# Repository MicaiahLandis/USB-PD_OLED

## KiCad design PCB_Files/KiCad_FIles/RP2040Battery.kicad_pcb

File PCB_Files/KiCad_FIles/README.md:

This Folder Had All KiCad Project files

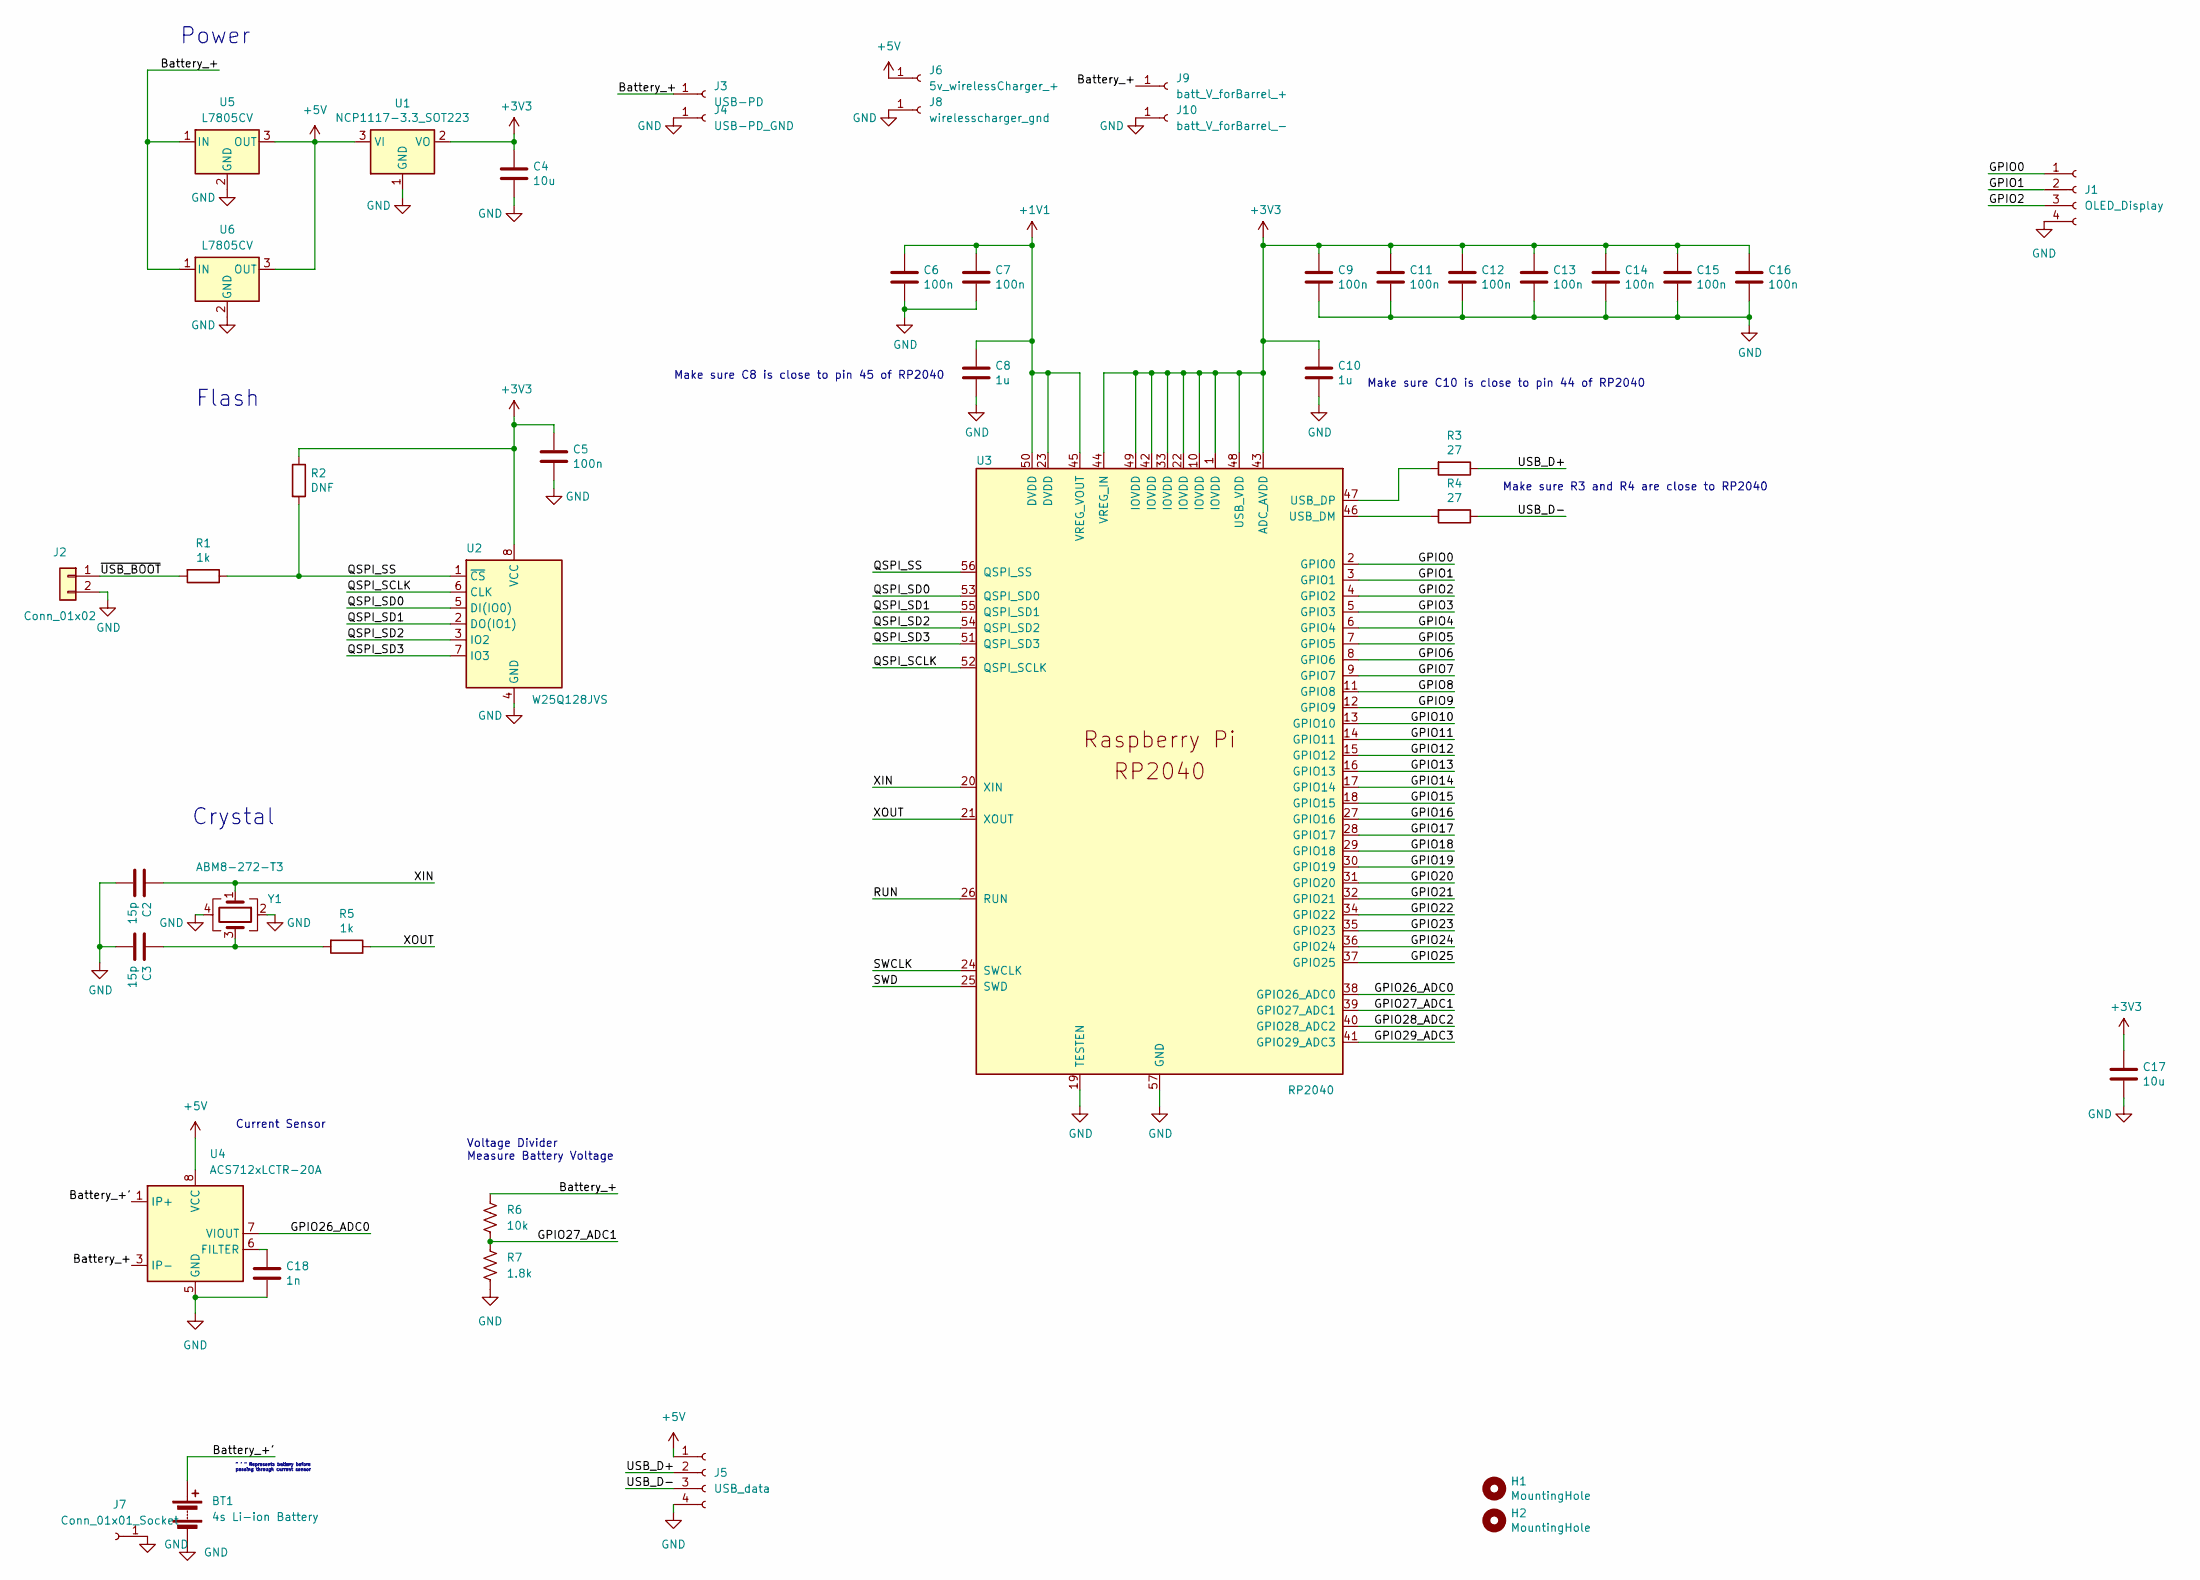
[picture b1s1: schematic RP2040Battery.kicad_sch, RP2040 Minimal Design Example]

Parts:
BT1: 4s Li-ion Battery; TestPoint_Pad_4.0x4.0mm
C2, C3: 15p; C_0402_1005Metric
C4, C17: 10u; C_0805_2012Metric
C5, C6, C7, C9, C11, C12, C13, C14, C15, C16: 100n; C_0402_1005Metric
C8, C10: 1u; C_0402_1005Metric
C18: 1n; C_0402_1005Metric
H1, H2: MountingHole; MountingHole_2.7mm_M2.5
J1: OLED_Display; PinHeader_1x04_P2.54mm_Vertical
J2: Conn_01x02; PinHeader_1x02_P2.54mm_Vertical
J3: USB-PD; SolderWire-2.5sqmm_1x01_D2.4mm_OD3.6mm
J4: USB-PD_GND; SolderWire-2.5sqmm_1x01_D2.4mm_OD3.6mm
J5: USB_data; PinHeader_1x04_P2.54mm_Vertical
J6: 5v_wirelessCharger_+; TestPoint_Pad_2.0x2.0mm
J7: Conn_01x01_Socket; TestPoint_Pad_4.0x4.0mm
J8: wirelesscharger_gnd; TestPoint_Pad_2.0x2.0mm
J9: batt_V_forBarrel_+; TestPoint_Pad_2.0x2.0mm
J10: batt_V_forBarrel_-; TestPoint_Pad_2.0x2.0mm
R1, R5: 1k; R_0402_1005Metric
R2: DNF; R_0402_1005Metric
R3, R4: 27; R_0402_1005Metric
R6: 10k; R_0402_1005Metric
R7: 1.8k; R_0402_1005Metric
U1: NCP1117-3.3_SOT223; SOT-223-3_TabPin2
U2: W25Q128JVS; SOIC-8_5.23x5.23mm_P1.27mm
U3: RP2040; RP2040-QFN-56
U4: ACS712xLCTR-20A; SOIC-8_3.9x4.9mm_P1.27mm
U5, U6: L7805CV; SIPAK-1EP_Horizontal_TabDown
Y1: ABM8-272-T3; Crystal_SMD_3225-4Pin_3.2x2.5mm

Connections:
+1V1: C6.1, C7.1, C8.1, U3.23 (DVDD), U3.45 (VREG_VOUT), U3.50 (DVDD)
+3V3: C4.1, C5.1, C9.1, C10.1, C11.1, C12.1, C13.1, C14.1, C15.1, C16.1, C17.1, R2.1, U1.2 (VO), U2.8 (VCC), U3.1 (IOVDD), U3.10 (IOVDD), U3.22 (IOVDD), U3.33 (IOVDD), U3.42 (IOVDD), U3.43 (ADC_AVDD), U3.44 (VREG_IN), U3.48 (USB_VDD), U3.49 (IOVDD)
+5V: J5.1, J6.1, U1.3 (VI), U4.8 (VCC), U5.3 (OUT), U6.3 (OUT)
/Battery_+: J3.1, J9.1, R6.1, U4.3 (IP-), U4.4 (IP-), U5.1 (IN), U6.1 (IN); also elsewhere on the board
/Battery_+': BT1.1 (+), U4.1 (IP+), U4.2 (IP+)
/GPIO0: J1.1, U3.2 (GPIO0)
/GPIO1: J1.2, U3.3 (GPIO1)
/GPIO2: J1.3, U3.4 (GPIO2)
/GPIO3: U3.5 (GPIO3)
/GPIO4: U3.6 (GPIO4)
/GPIO5: U3.7 (GPIO5)
/GPIO6: U3.8 (GPIO6)
/GPIO7: U3.9 (GPIO7)
/GPIO8: U3.11 (GPIO8)
/GPIO9: U3.12 (GPIO9)
/GPIO10: U3.13 (GPIO10)
/GPIO11: U3.14 (GPIO11)
/GPIO12: U3.15 (GPIO12)
/GPIO13: U3.16 (GPIO13)
/GPIO14: U3.17 (GPIO14)
/GPIO15: U3.18 (GPIO15)
/GPIO16: U3.27 (GPIO16)
/GPIO17: U3.28 (GPIO17)
/GPIO18: U3.29 (GPIO18)
/GPIO19: U3.30 (GPIO19)
/GPIO20: U3.31 (GPIO20)
/GPIO21: U3.32 (GPIO21)
/GPIO22: U3.34 (GPIO22)
/GPIO23: U3.35 (GPIO23)
/GPIO24: U3.36 (GPIO24)
/GPIO25: U3.37 (GPIO25)
/GPIO26_ADC0: U3.38 (GPIO26_ADC0), U4.7 (VIOUT)
/GPIO27_ADC1: R6.2, R7.1, U3.39 (GPIO27_ADC1)
/GPIO28_ADC2: U3.40 (GPIO28_ADC2)
/GPIO29_ADC3: U3.41 (GPIO29_ADC3)
/QSPI_SCLK: U2.6 (CLK), U3.52 (QSPI_SCLK)
/QSPI_SD0: U2.5 (DI(IO0)), U3.53 (QSPI_SD0)
/QSPI_SD1: U2.2 (DO(IO1)), U3.55 (QSPI_SD1)
/QSPI_SD2: U2.3 (IO2), U3.54 (QSPI_SD2)
/QSPI_SD3: U2.7 (IO3), U3.51 (QSPI_SD3)
/QSPI_SS: R1.1, R2.2, U2.1 (~CS), U3.56 (QSPI_SS)
/RUN: U3.26 (RUN)
/SWCLK: U3.24 (SWCLK)
/SWD: U3.25 (SWD)
/USB_D+: J5.2, R3.1
/USB_D-: J5.3, R4.1
/XIN: C2.1, U3.20 (XIN), Y1.1
/XOUT: R5.1, U3.21 (XOUT)
/~USB_BOOT: J2.1, R1.2
GND: BT1.2 (-), C2.2, C3.2, C4.2, C5.2, C6.2, C7.2, C8.2, C9.2, C10.2, C11.2, C12.2, C13.2, C14.2, C15.2, C16.2, C17.2, C18.2, J1.4, J2.2, J4.1, J5.4, J7.1, J8.1, J10.1, R7.2, U1.1 (GND), U2.4 (GND), U3.19 (TESTEN), U3.57 (GND), U4.5 (GND), U5.2 (GND), U6.2 (GND), Y1.2, Y1.4; also elsewhere on the board
unnamed: C3.1, R5.2, Y1.3
unnamed: R4.2, U3.46 (USB_DM)
unnamed: R3.2, U3.47 (USB_DP)
unnamed: C18.1, U4.6 (FILTER)

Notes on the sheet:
Power
Crystal
Make sure C8 is close to pin 45 of RP2040
Voltage Divider Measure Battery Voltage
Make sure C10 is close to pin 44 of RP2040
" ' " Represents battery before passing through current sensor
Make sure R3 and R4 are close to RP2040
Current Sensor
Flash

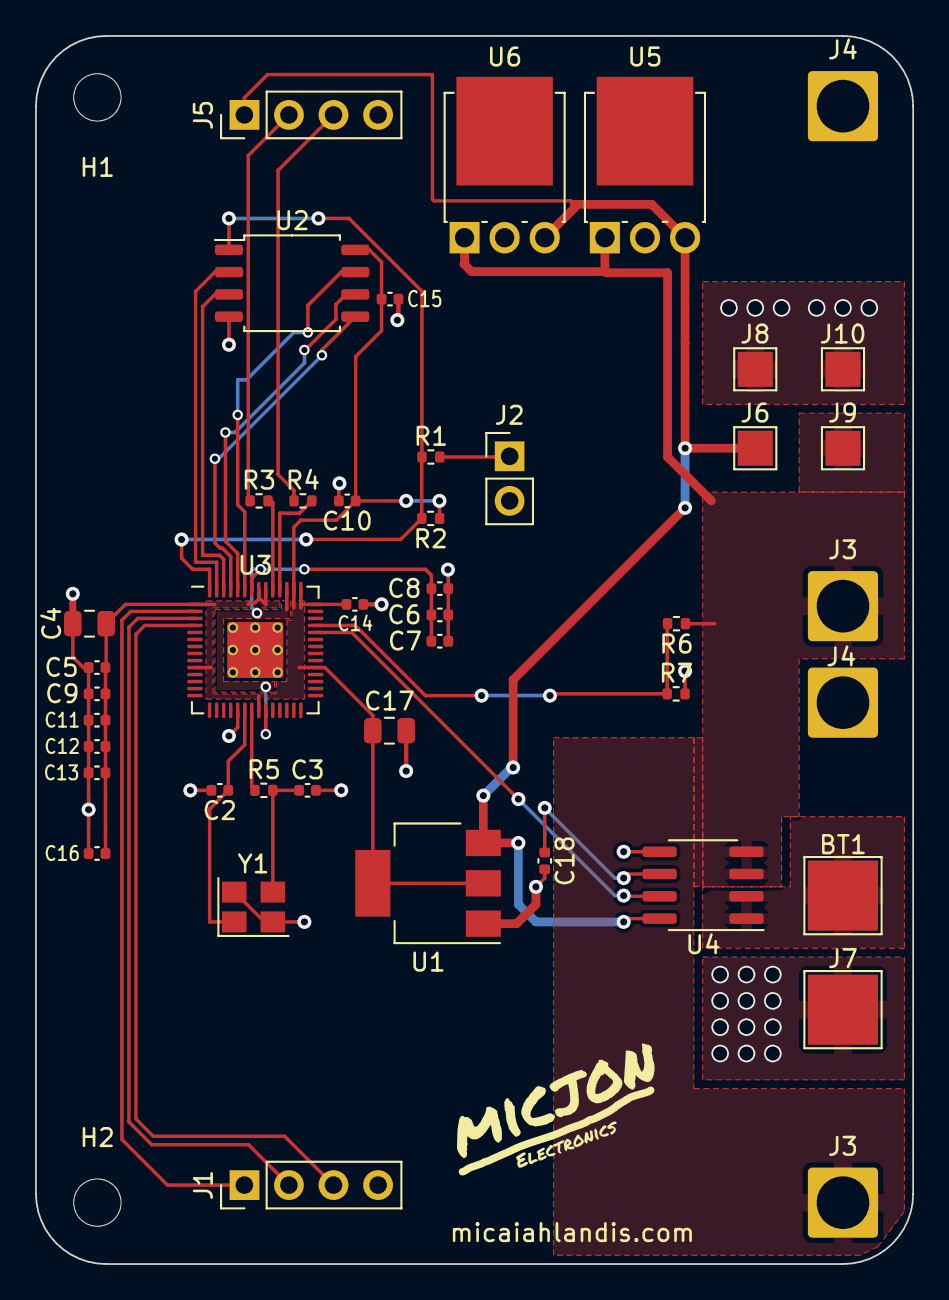
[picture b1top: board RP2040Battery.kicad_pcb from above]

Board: 2 copper layers, 50.0 x 70.0 mm, 46 parts (0 on the bottom side), 26 nets.

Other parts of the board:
J3#2: USB-PD; SolderWire-2.5sqmm_1x01_D2.4mm_OD3.6mm
J4#2: USB-PD_GND; SolderWire-2.5sqmm_1x01_D2.4mm_OD3.6mm

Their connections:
/Battery_+: J3#2.1; also elsewhere on the board
GND: J4#2.1; also elsewhere on the board

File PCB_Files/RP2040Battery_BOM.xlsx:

Comment | Designator | Footprint | JLCPCB Part #（optional）
15p | C2,C3 | Capacitor_SMD:C_0402_1005Metric
10u | C4 | Capacitor_SMD:C_0805_2012Metric
100n | C5 | Capacitor_SMD:C_0402_1005Metric
100n | C6,C7 | Capacitor_SMD:C_0402_1005Metric
1u | C8 | Capacitor_SMD:C_0402_1005Metric
100n | C9,C11,C12,C13,C14,C15,C16 | Capacitor_SMD:C_0402_1005Metric
1u | C10 | Capacitor_SMD:C_0402_1005Metric
10u | C17 | Capacitor_SMD:C_0805_2012Metric
1n | C18 | Capacitor_SMD:C_0402_1005Metric
1k | R1 | Resistor_SMD:R_0402_1005Metric
DNF | R2 | Resistor_SMD:R_0402_1005Metric
27 | R3 | Resistor_SMD:R_0402_1005Metric
27 | R4 | Resistor_SMD:R_0402_1005Metric
1k | R5 | Resistor_SMD:R_0402_1005Metric
10k | R6 | Resistor_SMD:R_0402_1005Metric
1.8k | R7 | Resistor_SMD:R_0402_1005Metric
NCP1117-3.3_SOT223 | U1 | Package_TO_SOT_SMD:SOT-223-3_TabPin2
W25Q128JVS | U2 | Package_SO:SOIC-8_5.23x5.23mm_P1.27mm
RP2040 | U3 | raspberry:RP2040-QFN-56
ACS712xLCTR-20A | U4 | Package_SO:SOIC-8_3.9x4.9mm_P1.27mm
ABM8-272-T3 | Y1 | Crystal:Crystal_SMD_3225-4Pin_3.2x2.5mm

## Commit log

2024-05-09 RP2040 Micropython code
    This includes the Main.py and ssd1306 for the OLED display. By putting both of these on a rp2040 running micro python a display can you used to show voltage and temperature, along with a real time ba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
2024-05-09 First PCB Design
    I did not order any of these because I placed many capacitors in the wrong locations.
2024-05-09 First micropython code
    This code will work with a 128x32 OLED display to show voltage and temperature. It also gives a battery visual of remaining capacity. A start to a sleeping code is implemented as well but does not wa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
2024-05-10 Update
    small changes
2024-05-24 Create KiCad_Files
2024-05-24 Add files via upload
    up to date with first physical pcb
